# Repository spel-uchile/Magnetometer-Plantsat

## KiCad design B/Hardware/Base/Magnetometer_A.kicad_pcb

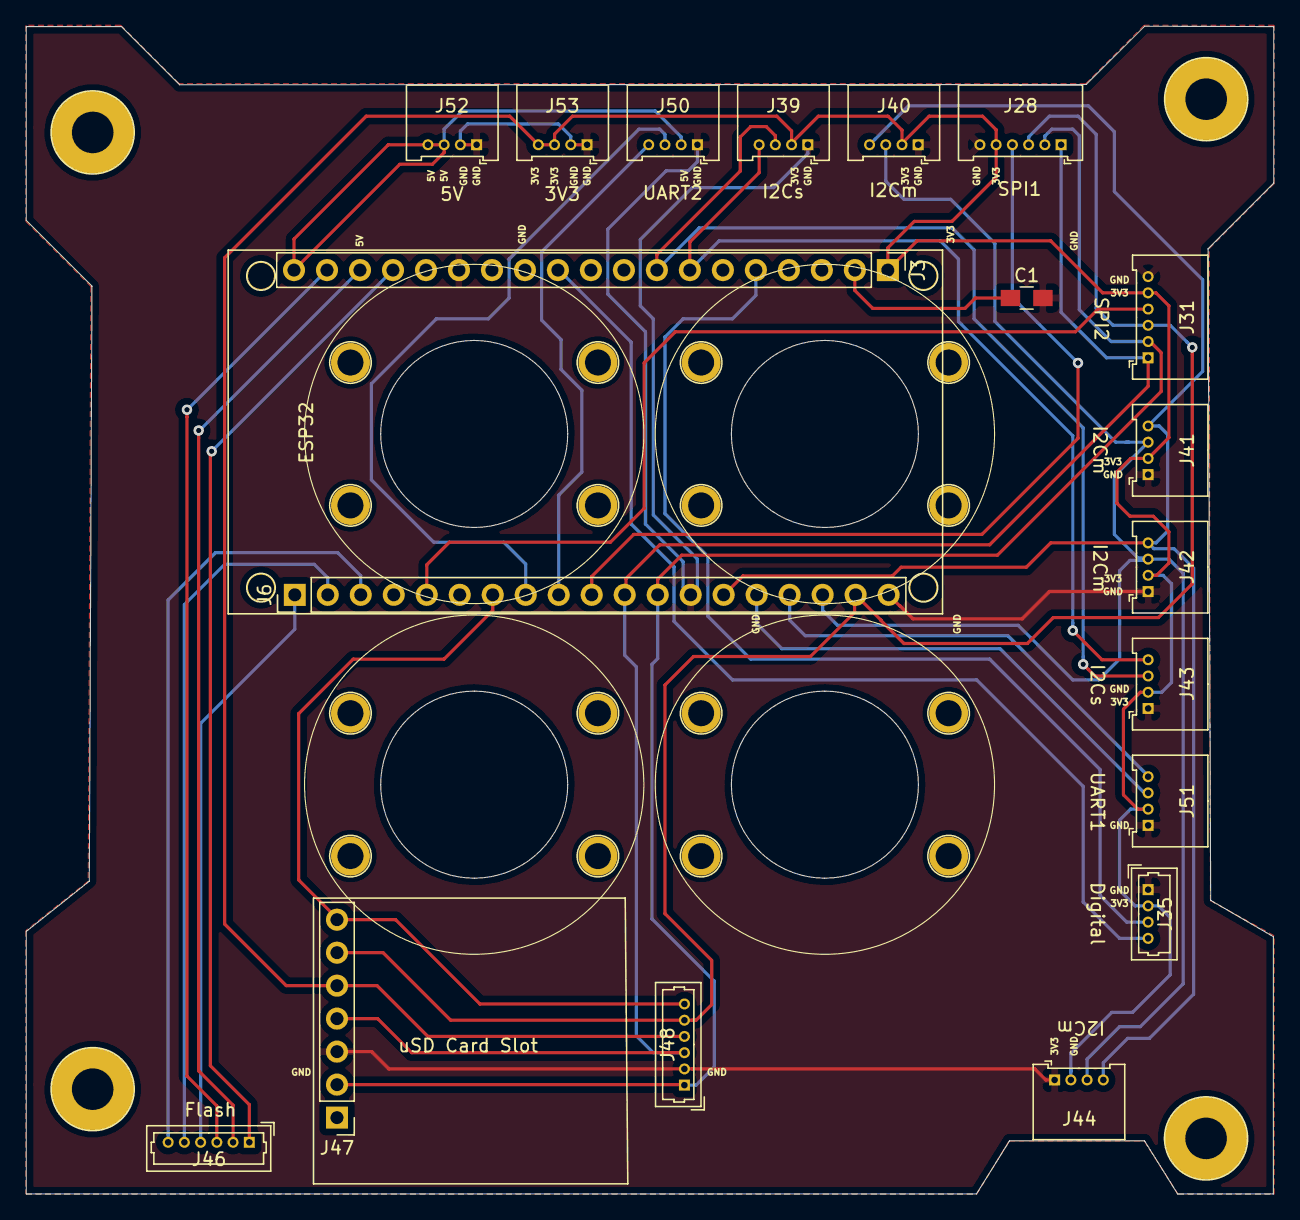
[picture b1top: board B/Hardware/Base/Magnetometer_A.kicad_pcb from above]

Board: 2 copper layers, 96.0 x 89.9 mm, 19 parts (0 on the bottom side), 26 nets.

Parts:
C1: 10uF; C_0805_HandSoldering
J3, J6: Conn_01x19_Female; Pin_Header_Straight_1x19_Pitch2.54mm
J28, J31: Conn_01x06_Male; Molex_PicoBlade_53048-0610_06x1.25mm_Angled
J35: Conn_01x04_Male; Molex_PicoBlade_53047-0410_04x1.25mm_Straight
J39, J40, J41, J42, J43, J44, J50, J51, J52, J53: Conn_01x04_Male; Molex_PicoBlade_53048-0410_04x1.25mm_Angled
J46, J48: Conn_01x06_Male; Molex_PicoBlade_53047-0610_06x1.25mm_Straight
J47: Conn_01x07_Male; Pin_Header_Straight_1x07_Pitch2.54mm

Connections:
2: J6.5, J31.4
3V3: J3.1, J28.5, J31.5, J35.2, J39.2, J40.2, J41.2, J42.2, J43.2, J44.2, J47.5, J48.4, J51.2, J53.3, J53.4
4: J6.7, J47.7, J48.6
5: J6.10, J28.4
5V: J3.19, J50.2, J52.3, J52.4
16: J6.8, J50.3
17: J6.9, J50.4
18: J6.11, J28.1, J31.1, J47.4, J48.3
19: J6.12, J28.2, J31.2, J47.2, J48.1
21: J6.14, J40.4, J41.4, J42.4, J44.4
22: J6.17, J40.3, J41.3, J42.3, J44.3
23: J6.18, J28.3, J31.3, J47.6, J48.5
27: J3.11, J35.4
32: J3.7, J39.4, J43.4
33: J3.8, J39.3, J43.3
34: J3.5, J35.3
CD_CLK: J6.1, J46.4
CD_CMD: J3.18, J46.3
D2: J3.16, J46.1
D3: J3.17, J46.2
EN: C1.1, J3.2
GND: C1.2, J3.14, J6.13, J6.19, J28.6, J31.6, J35.1, J39.1, J40.1, J41.1, J42.1, J43.1, J44.1, J47.3, J48.2, J50.1, J51.1, J52.1, J52.2, J53.1, J53.2
RX: J6.15, J51.3
SD_DATA_0: J6.2, J46.5
SD_SATA_1: J6.3, J46.6
TX: J6.16, J51.4

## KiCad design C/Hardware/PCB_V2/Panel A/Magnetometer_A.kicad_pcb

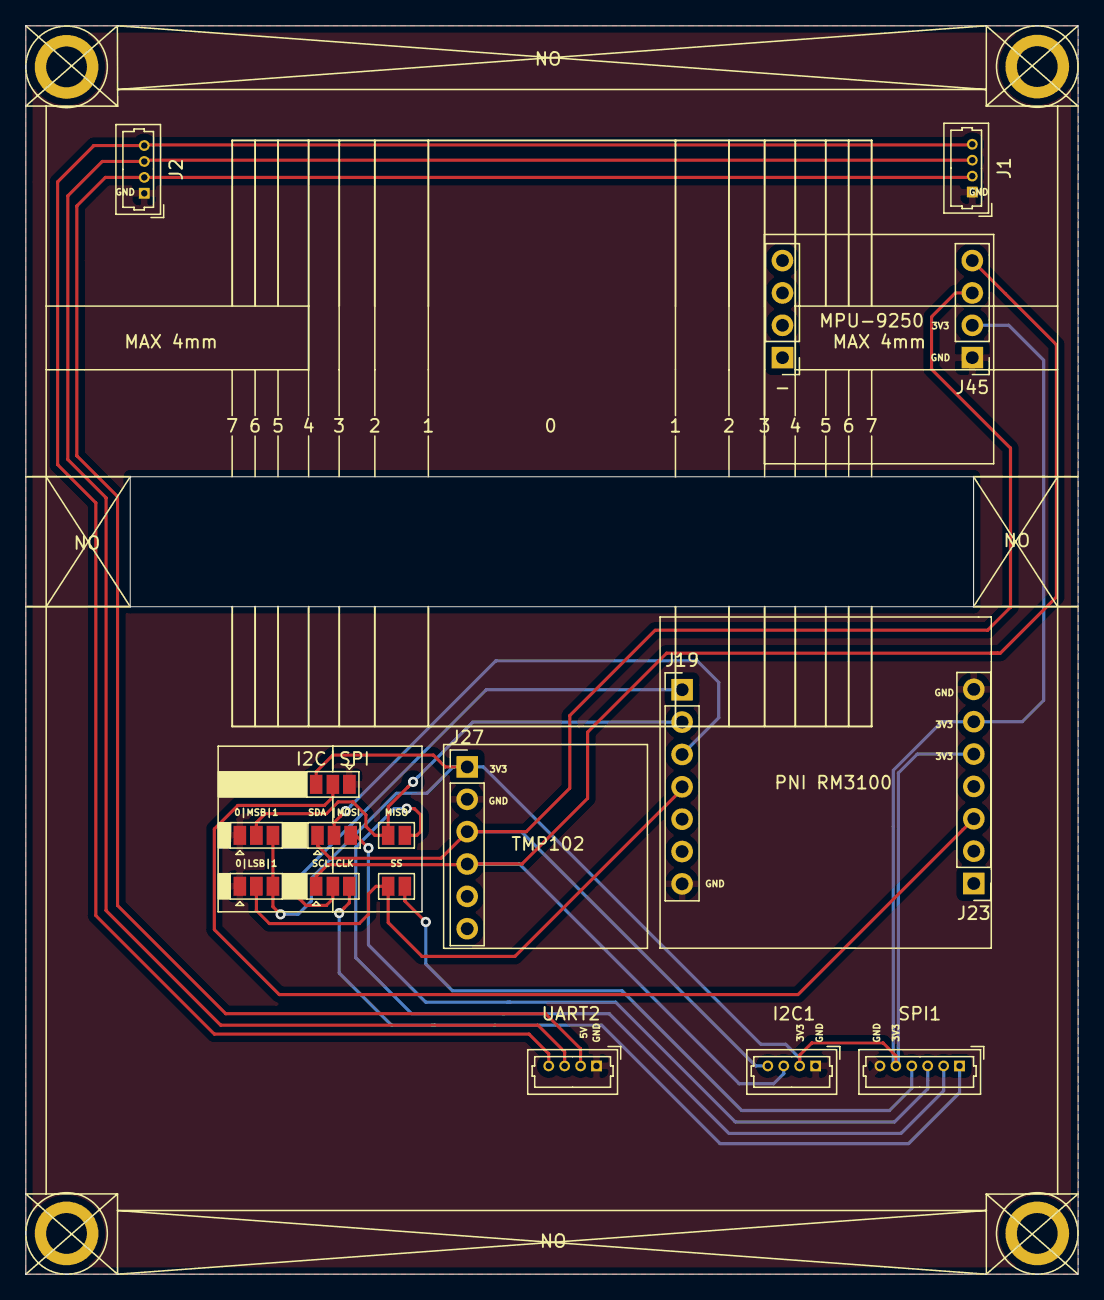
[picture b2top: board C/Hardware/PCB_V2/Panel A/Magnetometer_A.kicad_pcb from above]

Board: 2 copper layers, 82.6 x 98.0 mm, 17 parts (0 on the bottom side), 16 nets.

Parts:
0|LSB|1, 0|MSB|1: Conn_01x03_Male; SolderJumper-3_P1.3mm_Open_Pad1.0x1.5mm
-: Pin_Header_Straight_1x04_Pitch2.54mm
I2C1: Conn_01x04_Male; Molex_PicoBlade_53047-0410_04x1.25mm_Straight
I2C|SPI: Conn_01x03_Male; SolderJumper-3_P1.3mm_Open_Pad1.0x1.5mm
J1, J2: Conn_01x04_Male; Molex_PicoBlade_53047-0410_04x1.25mm_Straight
J19, J23: Conn_01x07_Female; Pin_Header_Straight_1x07_Pitch2.54mm
J27: Conn_01x06_Female; Pin_Header_Straight_1x06_Pitch2.54mm
J45: Conn_01x04_Male; Pin_Header_Straight_1x04_Pitch2.54mm
MISO: Conn_01x02_Male; SolderJumper-2_P1.3mm_Open_Pad1.0x1.5mm
SCL|CLK: Conn_01x03_Male; SolderJumper-3_P1.3mm_Open_Pad1.0x1.5mm
SDA |MOSI: Conn_01x03_Male; SolderJumper-3_P1.3mm_Open_Pad1.0x1.5mm
SPI1: Conn_01x06_Male; Molex_PicoBlade_53047-0610_06x1.25mm_Straight
SS: Conn_01x02_Male; SolderJumper-2_P1.3mm_Open_Pad1.0x1.5mm
UART2: Conn_01x04_male; Molex_PicoBlade_53047-0410_04x1.25mm_Straight

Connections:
3V3: 0|LSB|1.3, 0|MSB|1.3, I2C1.2, I2C|SPI.3, J23.5, J23.6, J27.1, J45.2, SPI1.5
5: SPI1.4, SS.2
5V: J1.2, J2.2, UART2.2
16: J1.3, J2.3, UART2.3
17: J1.4, J2.4, UART2.4
18: SCL|CLK.3, SPI1.1
19: MISO.2, SPI1.2
21: I2C1.4, J27.3, J45.3, SDA |MOSI.1
22: I2C1.3, J27.4, J45.4, SCL|CLK.1
23: SDA |MOSI.3, SPI1.3
GND: 0|LSB|1.1, 0|MSB|1.1, I2C1.1, I2C|SPI.1, J1.1, J2.1, J19.7, J23.7, J27.2, J45.1, SPI1.6, UART2.1
RM1CLK: J19.1, SCL|CLK.2
RM1EN: I2C|SPI.2, J23.3
RM1MISO: 0|MSB|1.2, J19.2, MISO.1
RM1MOSI: J19.3, SDA |MOSI.2
RM1SS: 0|LSB|1.2, J19.4, SS.1

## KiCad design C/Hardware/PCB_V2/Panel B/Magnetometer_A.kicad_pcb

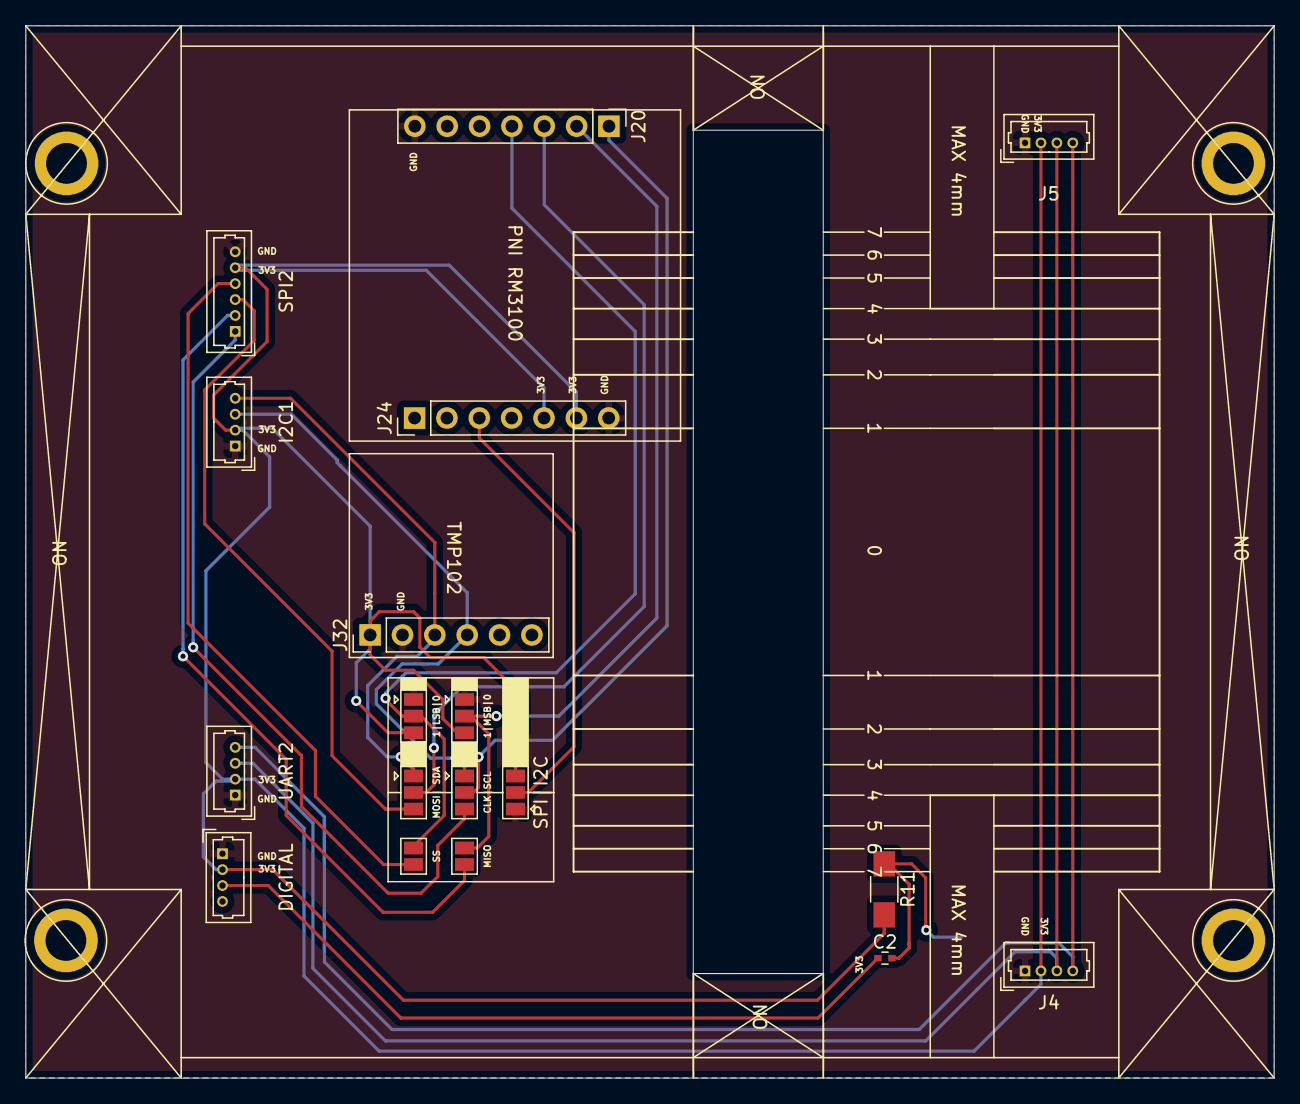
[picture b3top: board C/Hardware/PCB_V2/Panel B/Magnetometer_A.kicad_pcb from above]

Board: 2 copper layers, 98.0 x 82.6 mm, 19 parts (1 on the bottom side), 17 nets.

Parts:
1|LSB|0, 1|MSB|0: Conn_01x03_Male; SolderJumper-3_P1.3mm_Open_Pad1.0x1.5mm
C2: 1uF; C_0402
CLK|SCL: Conn_01x03_Male; SolderJumper-3_P1.3mm_Open_Pad1.0x1.5mm
DIGITAL: Conn_01x04_Male; Molex_PicoBlade_53047-0410_04x1.25mm_Straight
I2C1: Conn_01x04_Male; Molex_PicoBlade_53047-0410_04x1.25mm_Straight
J4, J5: Conn_01x04_Male; Molex_PicoBlade_53047-0410_04x1.25mm_Straight
J20, J24: Conn_01x07_Female; Pin_Header_Straight_1x07_Pitch2.54mm
J32: Conn_01x06_Female; Pin_Header_Straight_1x06_Pitch2.54mm
MISO: Conn_01x02_Male; SolderJumper-2_P1.3mm_Open_Pad1.0x1.5mm
MK1: Microphone_Condenser; SolderJumper-2_P1.3mm_Open_Pad1.0x1.5mm
MOSI| SDA: Conn_01x03_Male; SolderJumper-3_P1.3mm_Open_Pad1.0x1.5mm
R11: 2K2R; R_1206_HandSoldering
SPI2: Conn_01x06_Male; Molex_PicoBlade_53047-0610_06x1.25mm_Straight
SPI|I2C: Conn_01x03_Male; SolderJumper-3_P1.3mm_Open_Pad1.0x1.5mm
SS: Conn_01x02_Male; SolderJumper-2_P1.3mm_Open_Pad1.0x1.5mm
UART2: Conn_01x04_Male; Molex_PicoBlade_53047-0410_04x1.25mm_Straight

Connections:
2: SPI2.4, SS.2
3V3: 1|LSB|0.3, 1|MSB|0.3, DIGITAL.2, I2C1.2, J4.2, J5.2, J24.5, J24.6, J32.1, R11.2, SPI2.5, SPI|I2C.3, UART2.2
18: CLK|SCL.3, SPI2.1
19: MISO.2, SPI2.2
21: I2C1.4, J32.3, MOSI| SDA.1
22: CLK|SCL.1, I2C1.3, J32.4
23: MOSI| SDA.3, SPI2.3
34: C2.1, DIGITAL.3
GND: 1|LSB|0.1, 1|MSB|0.1, DIGITAL.1, I2C1.1, J4.1, J5.1, J20.7, J24.7, J32.2, MK1.1, SPI2.6, SPI|I2C.1, UART2.1
unnamed: C2.2, MK1.2, R11.1
RM2CLK: CLK|SCL.2, J20.1
RM2EN: J24.3, SPI|I2C.2
RM2MISO: 1|MSB|0.2, J20.2, MISO.1
RM2MOSI: J20.3, MOSI| SDA.2
RM2SS: 1|LSB|0.2, J20.4, SS.1
RX: J4.3, J5.3, UART2.3
TX: J4.4, J5.4, UART2.4

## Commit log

2021-07-03 First Commit
    Following the project development cycle
2021-07-13 Python Implementation for MAG in RPi
    Python sketch for use the PNI RM3100 in a Raspberry Pi
2021-11-05 Add temp driver
